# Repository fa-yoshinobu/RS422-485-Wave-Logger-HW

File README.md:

# RS-422／RS-485 波形ロガー | Rev.1

RS-422と2線・4線式RS-485の通信と差動波形、絶縁CAN（DeviceNet対応）のフレームをmicroSDに記録するロガー。通常は受信専用で、RS-485とCANの送信は切り離した試験回線で行う設計です。

## 現在の状況

Rev.1の基板と製造用データを作成済みです。DRC違反・未配線・回路図との不一致は各0件。ERCはエラー0件、警告618件。裏面74点を工場実装し、挿入部品と抵抗24点などを手はんだする構成です。波形記録の性能とケースへの実装は試作機で確認します。[入稿ファイルと確認結果](docs/Rev1-order-estimate.md#入稿ファイル)

## 接続例

[RS-422](docs/Wiring-RS422.md) ・ [RS-485（2線式・4線式）](docs/Wiring-RS485.md) ・ [Classical CAN](docs/Wiring-CAN.md) ・ [DeviceNet](docs/Wiring-DeviceNet.md)

各ガイドには受信、差動波形の測定、専用回線での試験送信の結線例があります。背面の端子台は、電線差込口を正面にして電源ジャックが左に見える向きで確認します。[端子番号と信号名の対応図](docs/wiring/Rear-Terminals.png)

端子台本体の電線差込口とねじ穴の間に信号名を合わせられる[原寸ラベル（仮合わせ用PDF）](docs/wiring/Terminal-Markers.pdf)があります。実寸で印刷して、穴の位置と表示の向きを確認できます。

## 設計・製造資料

| 目的 | 資料 |
| --- | --- |
| 手はんだ部品を用意する | [手はんだ部品表](pcb/manufacturing/Hand_Assembly_BOM.csv)（ソケットに装着するマイコンと液晶も記載） |
| JLCPCBに実装を依頼する | [JLCPCB実装部品表](pcb/manufacturing/JLCPCB-BOM.csv) |
| 回路を確認する | [回路図PDF](docs/RS422-485-Wave-Logger.pdf)・[KiCadデータ](pcb/) |
| 設計と寸法を確認する | [基板配置・取付寸法](docs/PCB-Rev1.md)・[両面の配線図PDF](docs/Rev1-copper.pdf)・[ケース組立](enclosure/drawings/Assembly.md) |
| 基板を製造・実装する | [入稿ファイルと発注条件](docs/Rev1-order-estimate.md#入稿ファイル)・[手はんだ実装図](enclosure/drawings/Hand-Solder-Assembly-Rev1.pdf) |
| 検証結果を確認する | [現行Rev.1の製造性検証](docs/verification/Rev1-DFM.md#2026-11-25-発注用データ)・[検証レポート一覧](docs/verification/) |

## 基板の外観

| 表面（操作側）の実装3D図 | 裏面（工場実装側）の実装3D図 |
| --- | --- |
|  |  |

| 表面の配線（F.Cu） | 裏面の配線（B.Cu） |
| --- | --- |
|  |  |

## 主な仕様

| 項目 | 内容 |
| --- | --- |
| RS-422／485 | 2ペアを受信し、差動波形と同相電圧を監視。差動波形は各2 MS/sが設計目標。通常測定時は裏面のSW1を全極OFF |
| CAN | 絶縁Classical CAN、DeviceNet対応。CAN側電源はJ6のV+／V−から供給。通常測定時はSW2の終端をOFF |
| 記録と操作 | microSD、12ピン液晶、ロータリーエンコーダー |
| 基板 | 100 × 100 mm、2層、板厚1.6 mm |
| 拡張端子 | Grove 2口（J7 I²C、J8 GPIO／ADC、各3.3 V） |
| ケース | 3Dプリント用。幅121.1 × 奥行110 × 高さ30.4 mm（樹脂ケース単体） |

**測定中はUSBでPCに接続しない。** 電源はDC出力が接地されていない安定化12 V・1 AのACアダプター（外径5.5 mm、内径2.1 mm、センタープラス）を使用します。ログは測定後にmicroSDを取り出して読み込みます。USBで設定・書き込みする前に、測定対象とACアダプターを外します。[対応アダプターの例](https://akizukidenshi.com/catalog/g/g117429/)

## 主な部品と選定理由

- **WeAct STM32H562RGT6**。差動波形2チャンネルの取り込み、通信の受信、基板上のmicroSDへの記録を1枚で受け持ちます。
- **SP3485とMCP6022**。SP3485で各ペアのデジタル信号を受信し、MCP6022と精密抵抗で差動波形をADCの入力範囲に収めます。
- **ADM3054**。CANの送受信を本体の回路から絶縁します。

## 3Dプリント用ケース

ふたはM3の熱圧入インサートとM3×6 mmねじ各4個で固定します。組立手順で、液晶の支持部品、背面端子の結線順、底面のDIPスイッチの向きを確認できます。

[ケース3D（GitHubブラウザー表示）](enclosure/3d-models/Case_Browser.stl)・[ケースSTEP](enclosure/3d-models/Wave-Logger-Case.step)・[編集用SolidCraftモデル](enclosure/3d-models/Wave-Logger-Case.sc)・[底STL](enclosure/print/Wave-Logger-Tray.stl)・[ふたSTL](enclosure/print/Wave-Logger-Lid.stl)・[組立手順とスイッチ・LEDの位置](enclosure/drawings/Assembly.md)・[基板を含む組立STEP](enclosure/3d-models/Wave-Logger-Assembly.step)

## ライセンス

本プロジェクトのオリジナルのハードウェア設計を **CERN Open Hardware Licence Version 2 – Weakly Reciprocal（`CERN-OHL-W-2.0`）** で公開します。[ライセンス全文](LICENSE)

対象は、KiCadの回路図・基板・プロジェクトとプロジェクト独自のライブラリ、編集用ケースモデル、独自の部品モデル、およびこれらに対応する製造・組立データのうち本プロジェクトが権利を持つ部分です。編集用ソースと製造・組立に必要な情報は、このリポジトリの [KiCadデータ](pcb/)・[ケースデータ](enclosure/)・[製造資料](docs/Rev1-order-estimate.md) にあります。[Source Location](https://github.com/fa-yoshinobu/RS422-485-Wave-Logger-HW)

第三者のデータには各権利者の利用条件が適用されます。KiCad標準ライブラリにはKiCadのライセンスが適用されます。[KiCadライブラリのライセンス](https://www.kicad.org/libraries/license/)

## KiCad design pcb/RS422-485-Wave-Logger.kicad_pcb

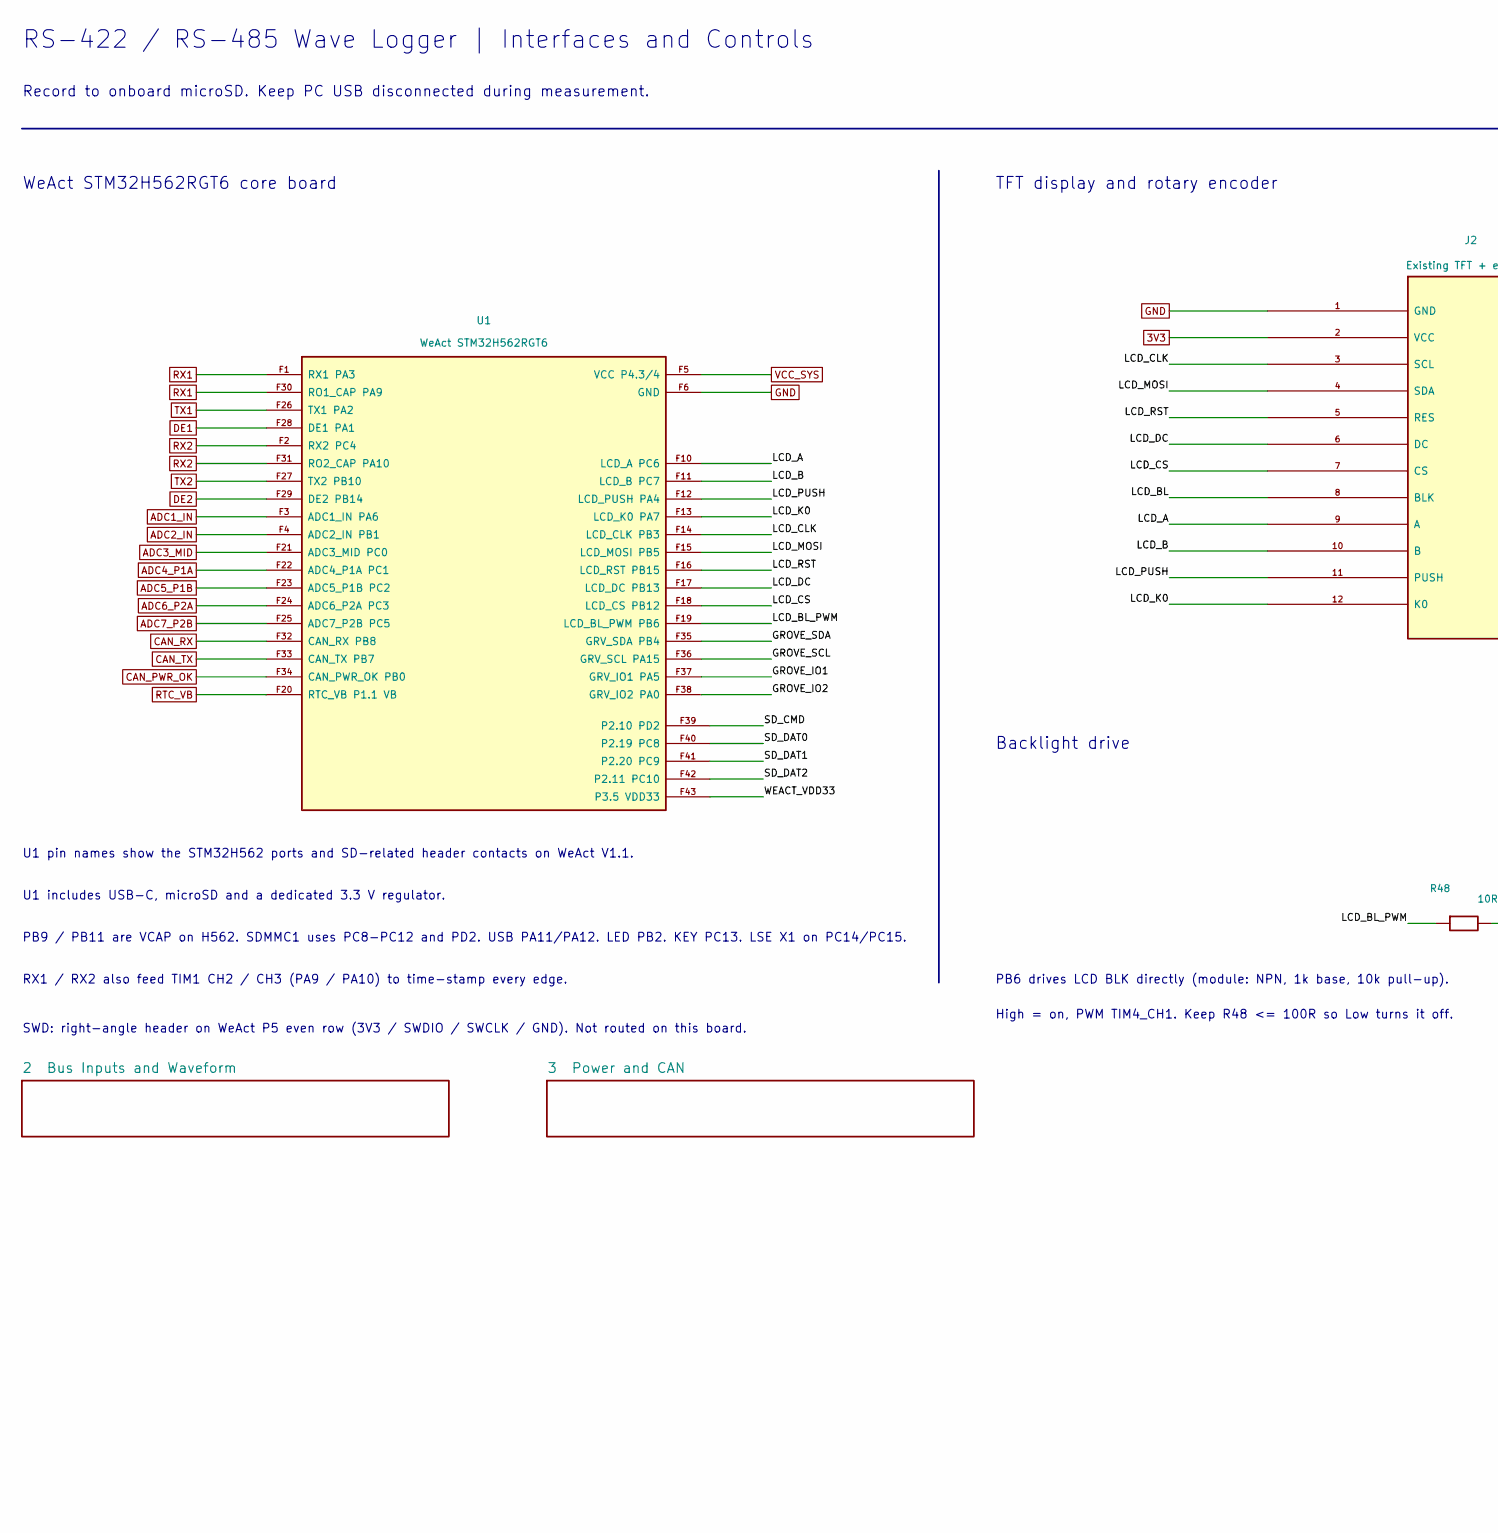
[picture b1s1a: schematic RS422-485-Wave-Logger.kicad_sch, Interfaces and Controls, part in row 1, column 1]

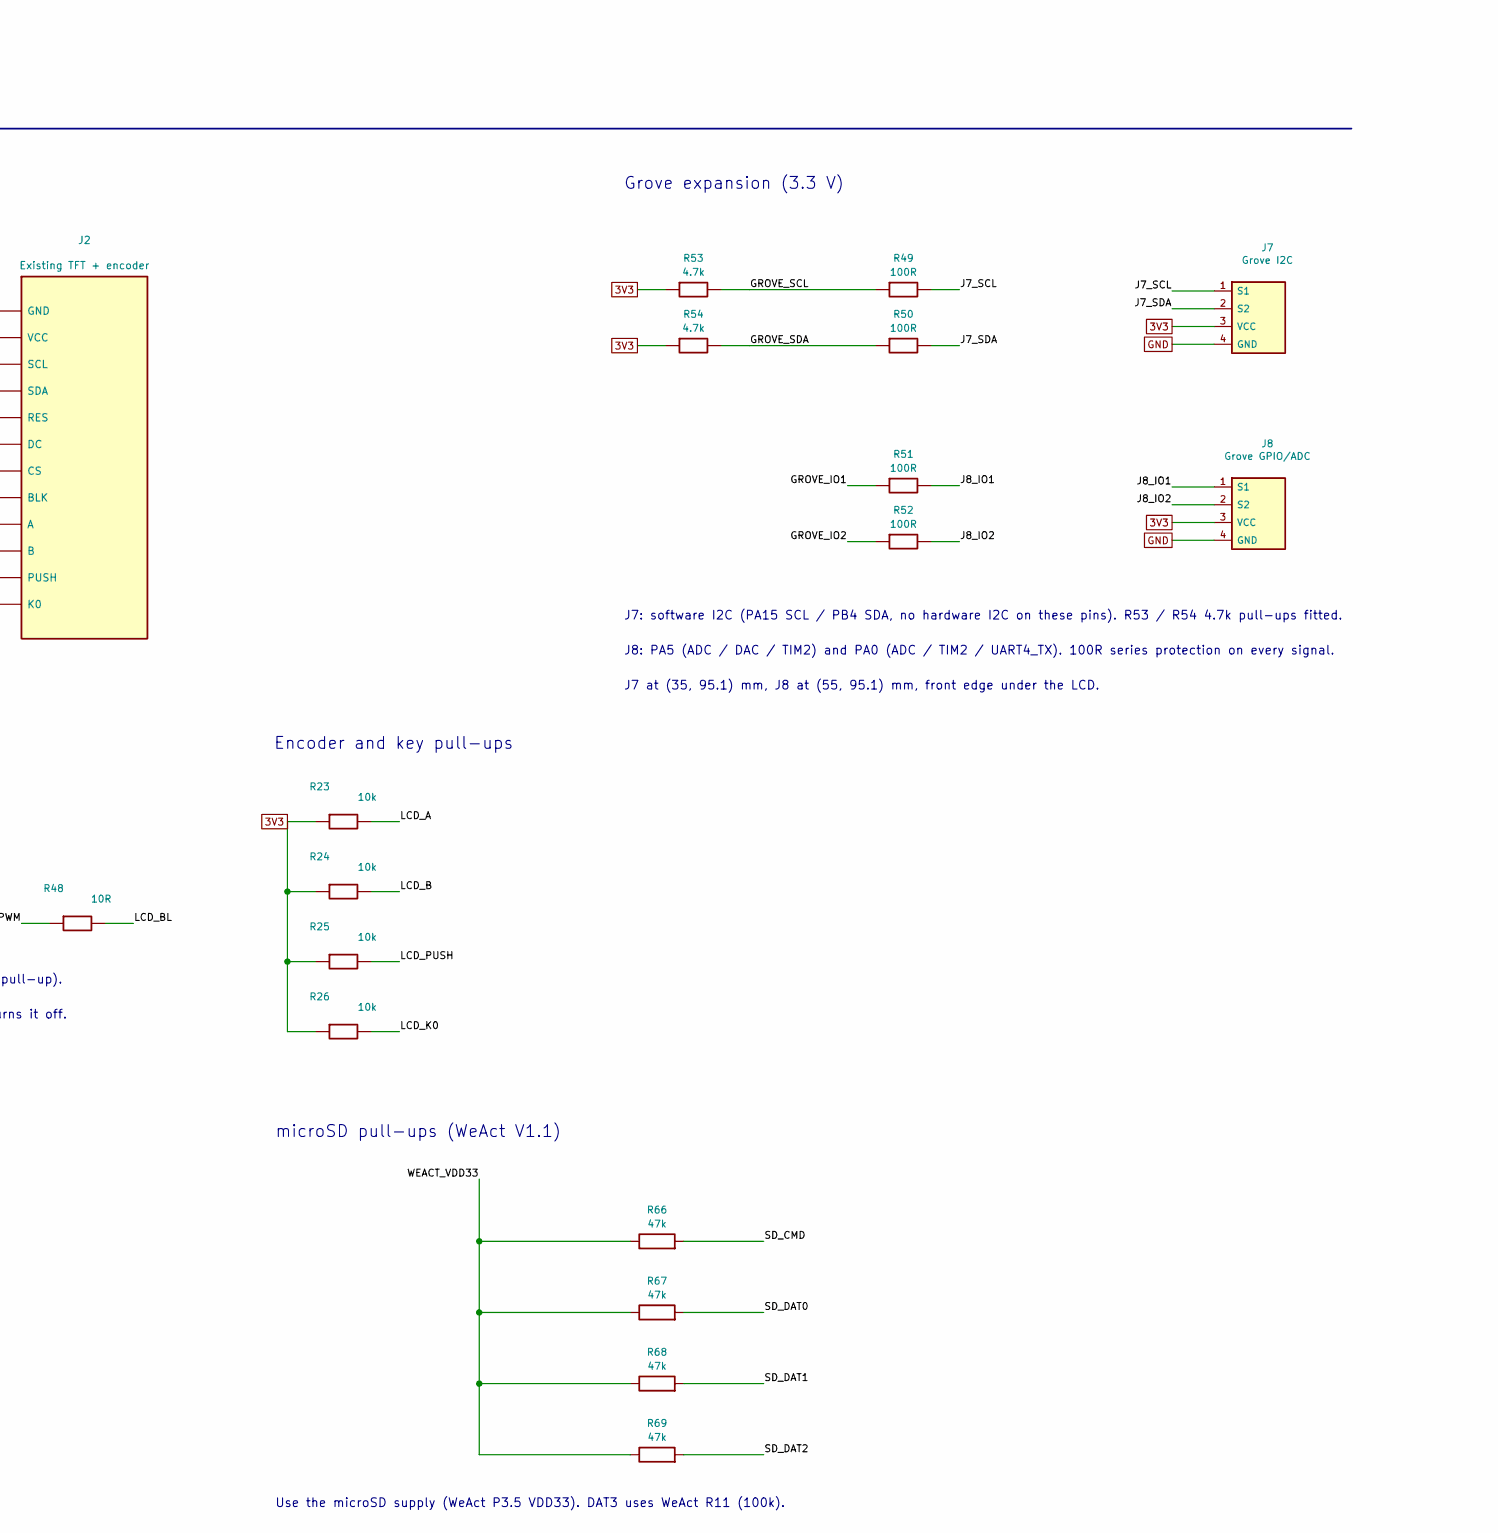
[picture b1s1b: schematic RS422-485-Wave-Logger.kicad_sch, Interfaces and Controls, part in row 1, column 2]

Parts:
J2: Existing TFT + encoder; TFT24_EC11_12P_90x43_Socket
J7: Grove I2C; Grove_110990037_RightAngle
J8: Grove GPIO/ADC; Grove_110990037_RightAngle
R23, R24, R25, R26: 10k; R_0603_1608Metric
R48: 10R; R_0603_1608Metric
R49, R50, R51, R52: 100R; R_0603_1608Metric
R53, R54: 4.7k; R_0603_1608Metric
R66, R68, R69: 47k; R_0603_1608Metric; LCSC C25819
R67: 47k; R_0603_1608Metric_Silk_Clearance; LCSC C25819
U1: WeAct STM32H562RGT6; WeAct_H562RG_V11

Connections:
3V3: J2.2 (VCC), J7.3 (VCC), J8.3 (VCC), R23.1, R24.1, R25.1, R26.1, R53.1, R54.1; also elsewhere on the board
/GROVE_IO1: R51.1, U1.F37 (GRV_IO1_PA5)
/GROVE_IO2: R52.1, U1.F38 (GRV_IO2_PA0)
/GROVE_SCL: R49.1, R53.2, U1.F36 (GRV_SCL_PA15)
/GROVE_SDA: R50.1, R54.2, U1.F35 (GRV_SDA_PB4)
/J7_SCL: J7.1 (S1), R49.2
/J7_SDA: J7.2 (S2), R50.2
/J8_IO1: J8.1 (S1), R51.2
/J8_IO2: J8.2 (S2), R52.2
/LCD_A: J2.9 (A), R23.2, U1.F10 (LCD_A_PC6)
/LCD_B: J2.10 (B), R24.2, U1.F11 (LCD_B_PC7)
/LCD_BL: J2.8 (BLK), R48.2
/LCD_BL_PWM: R48.1, U1.F19 (LCD_BL_PWM_PB6)
/LCD_CLK: J2.3 (SCL), U1.F14 (LCD_CLK_PB3)
/LCD_CS: J2.7 (CS), U1.F18 (LCD_CS_PB12)
/LCD_DC: J2.6 (DC), U1.F17 (LCD_DC_PB13)
/LCD_K0: J2.12 (K0), R26.2, U1.F13 (LCD_K0_PA7)
/LCD_MOSI: J2.4 (SDA), U1.F15 (LCD_MOSI_PB5)
/LCD_PUSH: J2.11 (PUSH), R25.2, U1.F12 (LCD_PUSH_PA4)
/LCD_RST: J2.5 (RES), U1.F16 (LCD_RST_PB15)
/SD_CMD: R66.2, U1.F39 (P2.10_PD2)
/SD_DAT0: R67.2, U1.F40 (P2.19_PC8)
/SD_DAT1: R68.2, U1.F41 (P2.20_PC9)
/SD_DAT2: R69.2, U1.F42 (P2.11_PC10)
/WEACT_VDD33: R66.1, R67.1, R68.1, R69.1, U1.F43 (P3.5_VDD33)
ADC1_IN: U1.F3 (ADC1_IN_PA6); also elsewhere on the board
ADC2_IN: U1.F4 (ADC2_IN_PB1); also elsewhere on the board
ADC3_MID: U1.F21 (ADC3_MID_PC0); also elsewhere on the board
ADC4_P1A: U1.F22 (ADC4_P1A_PC1); also elsewhere on the board
ADC5_P1B: U1.F23 (ADC5_P1B_PC2); also elsewhere on the board
ADC6_P2A: U1.F24 (ADC6_P2A_PC3); also elsewhere on the board
ADC7_P2B: U1.F25 (ADC7_P2B_PC5); also elsewhere on the board
CAN_PWR_OK: U1.F34 (CAN_PWR_OK_PB0); also elsewhere on the board
CAN_RX: U1.F32 (CAN_RX_PB8); also elsewhere on the board
CAN_TX: U1.F33 (CAN_TX_PB7); also elsewhere on the board
DE1: U1.F28 (DE1_PA1); also elsewhere on the board
DE2: U1.F29 (DE2_PB14); also elsewhere on the board
GND: J2.1 (GND), J7.4 (GND), J8.4 (GND), U1.F6 (GND); also elsewhere on the board
RTC_VB: U1.F20 (RTC_VB_P1.1_VB); also elsewhere on the board
RX1: U1.F1 (RX1_PA3), U1.F30 (RO1_CAP_PA9); also elsewhere on the board
RX2: U1.F2 (RX2_PC4), U1.F31 (RO2_CAP_PA10); also elsewhere on the board
TX1: U1.F26 (TX1_PA2); also elsewhere on the board
TX2: U1.F27 (TX2_PB10); also elsewhere on the board
VCC_SYS: U1.F5 (VCC_P4.3/4); also elsewhere on the board

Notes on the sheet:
RS-422 / RS-485 Wave Logger | Interfaces and Controls
Record to onboard microSD. Keep PC USB disconnected during measurement.
WeAct STM32H562RGT6 core board
TFT display and rotary encoder
Backlight drive
U1 pin names show the STM32H562 ports and SD-related header contacts on WeAct V1.1.
U1 includes USB-C, microSD and a dedicated 3.3 V regulator.
PB9 / PB11 are VCAP on H562. SDMMC1 uses PC8-PC12 and PD2. USB PA11/PA12. LED PB2. KEY PC13. LSE X1 on PC14/PC15.
RX1 / RX2 also feed TIM1 CH2 / CH3 (PA9 / PA10) to time-stamp every edge.
PB6 drives LCD BLK directly (module: NPN, 1k base, 10k pull-up).
High = on, PWM TIM4_CH1. Keep R48 <= 100R so Low turns it off.
Encoder and key pull-ups
SWD: right-angle header on WeAct P5 even row (3V3 / SWDIO / SWCLK / GND). Not routed on this board.
Grove expansion (3.3 V)
J7: software I2C (PA15 SCL / PB4 SDA, no hardware I2C on these pins). R53 / R54 4.7k pull-ups fitted.
J8: PA5 (ADC / DAC / TIM2) and PA0 (ADC / TIM2 / UART4_TX). 100R series protection on every signal.
J7 at (35, 95.1) mm, J8 at (55, 95.1) mm, front edge under the LCD.
microSD pull-ups (WeAct V1.1)
Use the microSD supply (WeAct P3.5 VDD33). DAT3 uses WeAct R11 (100k).

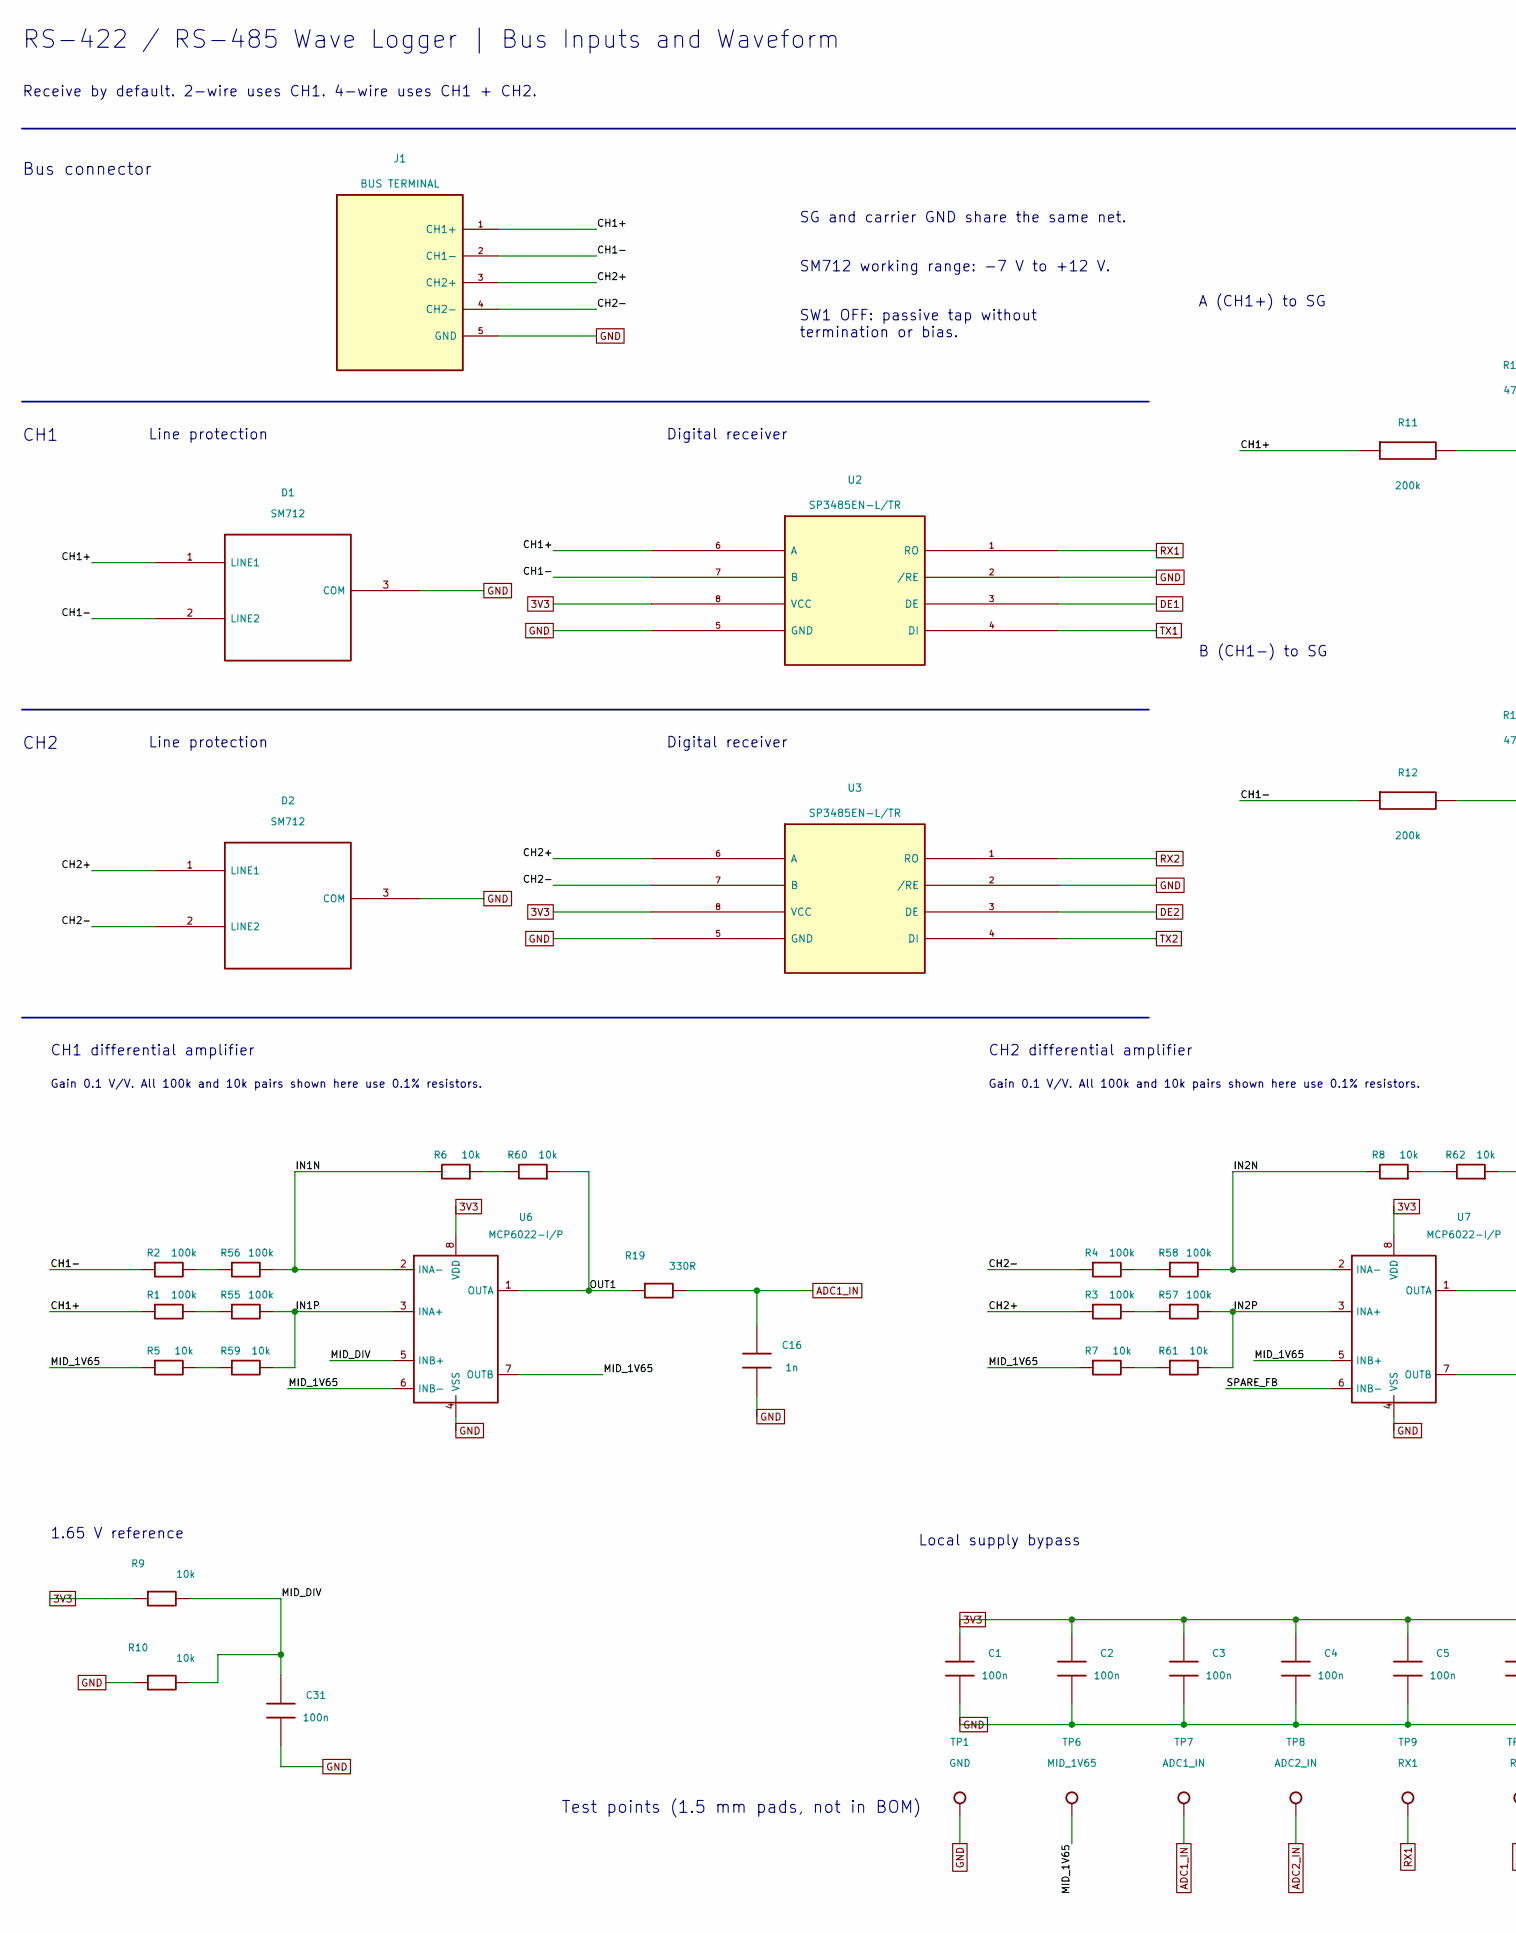
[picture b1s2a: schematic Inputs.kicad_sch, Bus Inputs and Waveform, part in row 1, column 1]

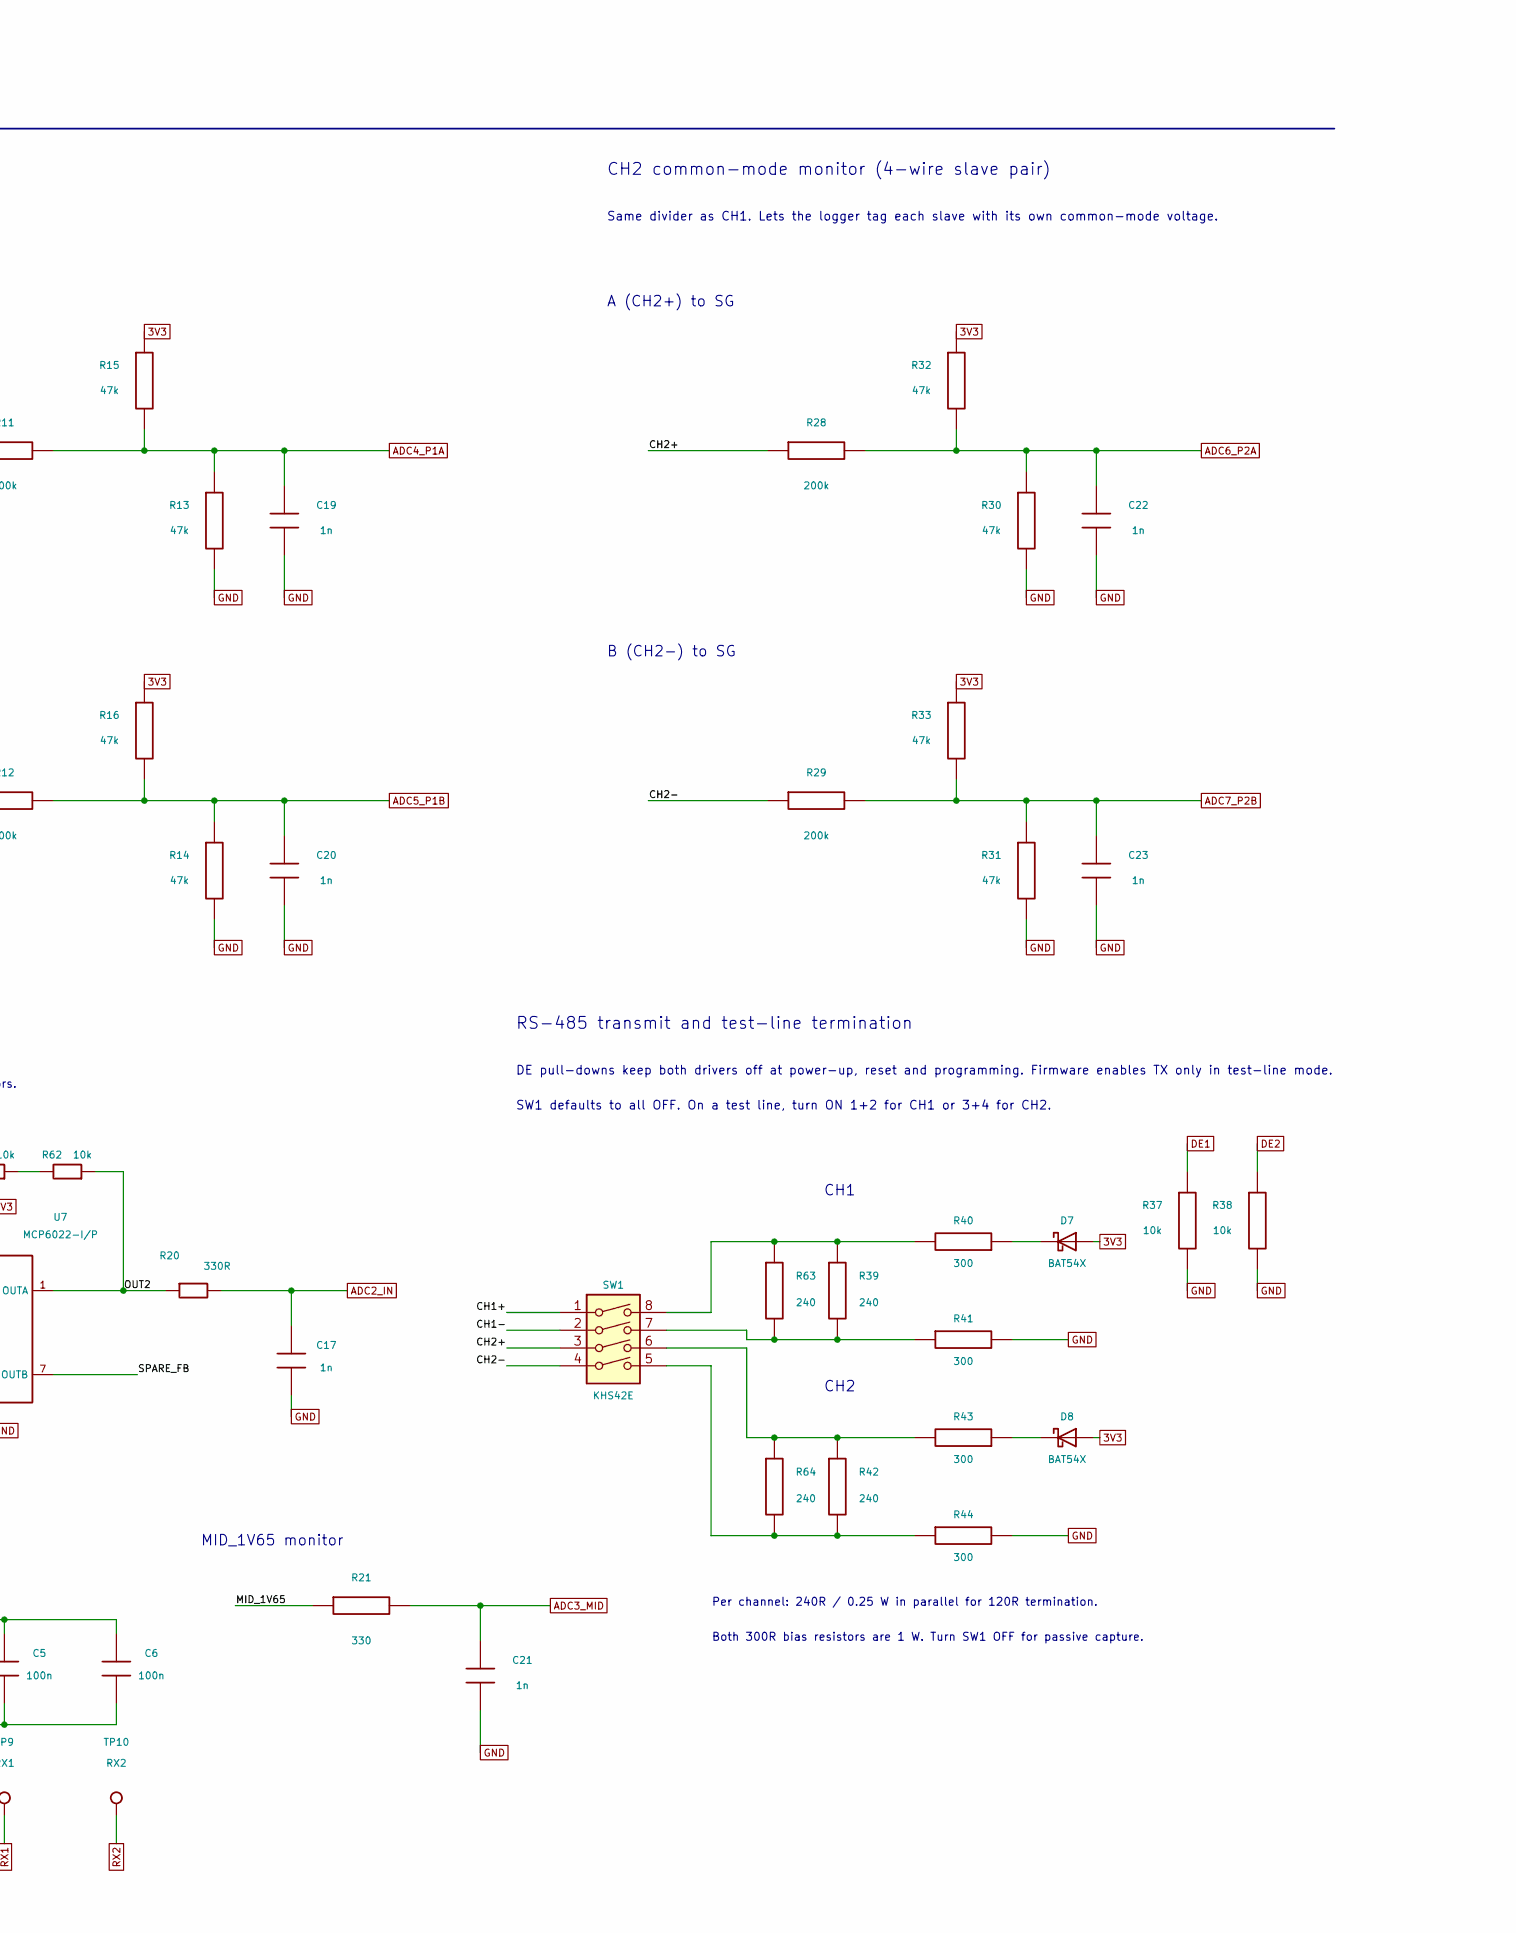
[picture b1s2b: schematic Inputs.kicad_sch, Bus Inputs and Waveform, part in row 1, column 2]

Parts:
C1, C2, C3, C4, C5, C6, C31: 100n; C_0603_1608Metric
C16, C17, C19, C20, C21, C22, C23: 1n; C_0603_1608Metric
D1, D2: SM712; SOT-23
D7, D8: BAT54X; D_SOD-523; MPN BAT54X; LCSC C19627026
J1: BUS TERMINAL; Akizuki_APF142_APF143_5P_P5.08
R1, R2, R3, R4, R55, R56, R57, R58: 100k; R_0805_2012Metric; Tolerance 0.1%; MPN RG2012N-104-B-T5
R5, R6, R7, R8, R59, R60, R61, R62: 10k; R_0805_2012Metric; Tolerance 0.1%; MPN RG2012-N-103-B-T5
R9, R10, R37, R38: 10k; R_0603_1608Metric
R11, R12, R28, R29: 200k; R_0603_1608Metric
R13, R14, R15, R16, R30, R31, R32, R33: 47k; R_0603_1608Metric
R19, R20: 330R; R_0603_1608Metric
R21: 330; R_0603_1608Metric
R39, R42, R63, R64: 240; R_Axial_DIN0204_L3.6mm_D1.6mm_P7.62mm_Horizontal; Tolerance 1%; MPN MFS25F240RB
R40, R41, R43, R44: 300; R_Axial_DIN0207_L6.3mm_D2.5mm_P10.16mm_Horizontal; Tolerance 1%; MPN MFU100F300RB
SW1: KHS42E; OTAX_KHS42E
TP1: GND; TestPoint_Pad_D1.5mm
TP6: MID_1V65; TestPoint_Pad_D1.5mm
TP7: ADC1_IN; TestPoint_Pad_D1.5mm
TP8: ADC2_IN; TestPoint_Pad_D1.5mm
TP9: RX1; TestPoint_Pad_D1.5mm
TP10: RX2; TestPoint_Pad_D1.5mm
U2, U3: SP3485EN-L/TR; SOIC-8_3.9x4.9mm_P1.27mm
U6, U7: MCP6022-I/P; DIP-8_W7.62mm

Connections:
3V3: C1.1, C2.1, C3.1, C4.1, C5.1, C6.1, D7.2 (A), D8.2 (A), R9.1, R15.1, R16.1, R32.1, R33.1, U2.8 (VCC), U3.8 (VCC), U6.8 (VDD), U7.8 (VDD); also elsewhere on the board
/2 Bus Inputs and Waveform/CH1+: D1.1 (LINE1), J1.1 (CH1+), R1.1, R11.1, SW1.1, U2.6 (A)
/2 Bus Inputs and Waveform/CH1-: D1.2 (LINE2), J1.2 (CH1-), R2.1, R12.1, SW1.2, U2.7 (B)
/2 Bus Inputs and Waveform/CH2+: D2.1 (LINE1), J1.3 (CH2+), R3.1, R28.1, SW1.3, U3.6 (A)
/2 Bus Inputs and Waveform/CH2-: D2.2 (LINE2), J1.4 (CH2-), R4.1, R29.1, SW1.4, U3.7 (B)
/2 Bus Inputs and Waveform/IN1N: R6.2, R56.2, U6.2 (INA-)
/2 Bus Inputs and Waveform/IN1P: R55.2, R59.2, U6.3 (INA+)
/2 Bus Inputs and Waveform/IN2N: R8.2, R58.2, U7.2 (INA-)
/2 Bus Inputs and Waveform/IN2P: R57.2, R61.2, U7.3 (INA+)
/2 Bus Inputs and Waveform/MID_1V65: R5.1, R7.1, R21.1, TP6.1 (1_1), U6.6 (INB-), U6.7 (OUTB), U7.5 (INB+)
/2 Bus Inputs and Waveform/MID_DIV: C31.1, R9.2, R10.2, U6.5 (INB+)
/2 Bus Inputs and Waveform/OUT1: R19.1, R60.1, U6.1 (OUTA)
/2 Bus Inputs and Waveform/OUT2: R20.1, R62.1, U7.1 (OUTA)
/2 Bus Inputs and Waveform/SPARE_FB: U7.6 (INB-), U7.7 (OUTB)
ADC1_IN: C16.1, R19.2, TP7.1 (1_1); also elsewhere on the board
ADC2_IN: C17.1, R20.2, TP8.1 (1_1); also elsewhere on the board
ADC3_MID: C21.1, R21.2; also elsewhere on the board
ADC4_P1A: C19.1, R11.2, R13.1, R15.2; also elsewhere on the board
ADC5_P1B: C20.1, R12.2, R14.1, R16.2; also elsewhere on the board
ADC6_P2A: C22.1, R28.2, R30.1, R32.2; also elsewhere on the board
ADC7_P2B: C23.1, R29.2, R31.1, R33.2; also elsewhere on the board
DE1: R37.1, U2.3 (DE); also elsewhere on the board
DE2: R38.1, U3.3 (DE); also elsewhere on the board
GND: C1.2, C2.2, C3.2, C4.2, C5.2, C6.2, C16.2, C17.2, C19.2, C20.2, C21.2, C22.2, C23.2, C31.2, D1.3 (COM), D2.3 (COM), J1.5 (GND), R10.1, R13.2, R14.2, R30.2, R31.2, R37.2, R38.2, R41.2, R44.2, TP1.1 (1_1), U2.2 (/RE), U2.5 (GND), U3.2 (/RE), U3.5 (GND), U6.4 (VSS), U7.4 (VSS); also elsewhere on the board
unnamed: D7.1 (K), R40.1
unnamed: D8.1 (K), R43.1
unnamed: R1.2, R55.1
unnamed: R2.2, R56.1
unnamed: R3.2, R57.1
unnamed: R4.2, R58.1
unnamed: R5.2, R59.1
unnamed: R6.1, R60.2
unnamed: R39.1, R40.2, R63.1, SW1.8
unnamed: R39.2, R41.1, R63.2, SW1.7
unnamed: R42.1, R43.2, R64.1, SW1.6
unnamed: R42.2, R44.1, R64.2, SW1.5
unnamed: R7.2, R61.1
unnamed: R8.1, R62.2
RX1: TP9.1 (1_1), U2.1 (RO); also elsewhere on the board
RX2: TP10.1 (1_1), U3.1 (RO); also elsewhere on the board
TX1: U2.4 (DI); also elsewhere on the board
TX2: U3.4 (DI); also elsewhere on the board

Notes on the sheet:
RS-422 / RS-485 Wave Logger | Bus Inputs and Waveform
Receive by default. 2-wire uses CH1. 4-wire uses CH1 + CH2.
Bus connector
SG and carrier GND share the same net.
SM712 working range: -7 V to +12 V.
SW1 OFF: passive tap without termination or bias.
CH1
Line protection
Digital receiver
CH2
A (CH1+) to SG
B (CH1-) to SG
MID_1V65 monitor
CH2 common-mode monitor (4-wire slave pair)
Same divider as CH1. Lets the logger tag each slave with its own common-mode voltage.
A (CH2+) to SG
B (CH2-) to SG
RS-485 transmit and test-line termination
DE pull-downs keep both drivers off at power-up, reset and programming. Firmware enables TX only in test-line mode.
SW1 defaults to all OFF. On a test line, turn ON 1+2 for CH1 or 3+4 for CH2.
Per channel: 240R / 0.25 W in parallel for 120R termination.
Both 300R bias resistors are 1 W. Turn SW1 OFF for passive capture.
CH1 differential amplifier
Gain 0.1 V/V. All 100k and 10k pairs shown here use 0.1% resistors.
1.65 V reference
CH2 differential amplifier
Local supply bypass
Test points (1.5 mm pads, not in BOM)
